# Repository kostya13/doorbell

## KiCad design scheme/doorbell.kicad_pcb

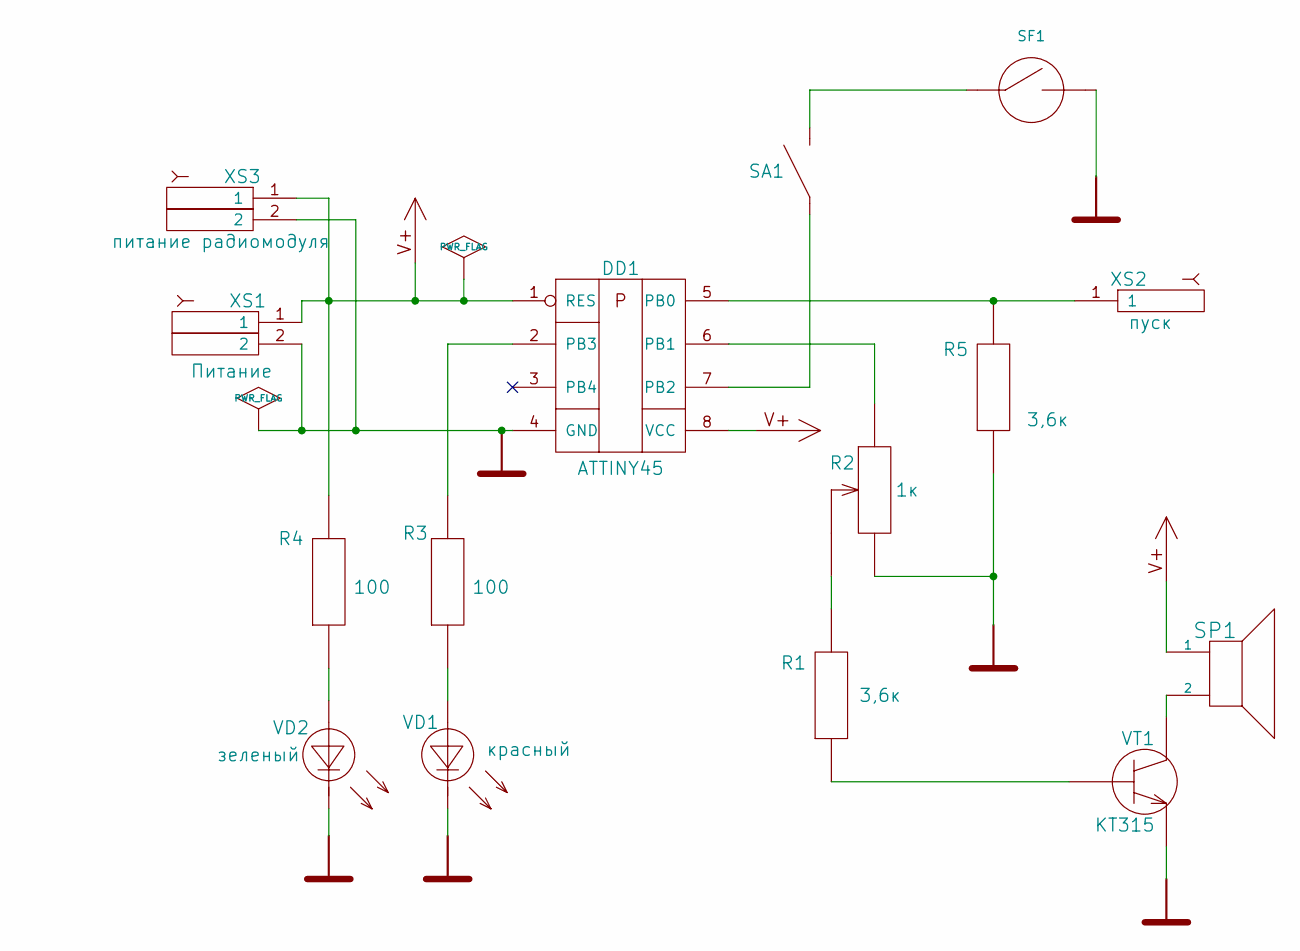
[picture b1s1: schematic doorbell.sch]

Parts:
DD1: ATTINY45
R1: 3,6к
R2: 1к
R3, R4: 100
R5: 3,6к
SA1: SA
SF1: SF
SP1: SPEAKER
VD1: красный
VD2: зеленый
VT1: КТ315
XS1: Питание
XS2: пуск
XS3: питание радиомодуля

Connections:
GND: DD1.4 (GND), R2.3, R5.1, SF1.1, VD1.1, VD2.1, VT1.3 (E), XS1.2, XS3.2
unnamed: R1.1, VT1.1 (B)
unnamed: R3.1, VD1.2
unnamed: R4.1, VD2.2
unnamed: DD1.2 (PB3), R3.2
unnamed: SP1.2, VT1.2 (C)
unnamed: DD1.6 (PB1), R2.1
unnamed: SA1.1, SF1.2
unnamed: R1.2, R2.2
unnamed: DD1.5 (PB0), R5.2, XS2.1
unnamed: DD1.7 (PB2), SA1.2
V+: DD1.1 (RES), DD1.8 (VCC), R4.2, SP1.1, XS1.1, XS3.1

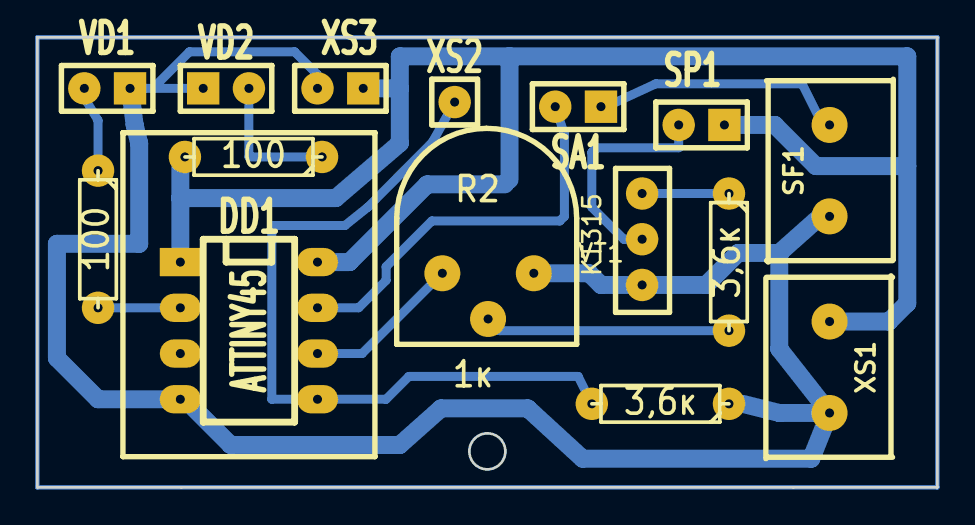
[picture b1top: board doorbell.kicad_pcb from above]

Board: 2 copper layers, 50.0 x 25.0 mm, 15 parts (0 on the bottom side), 12 nets.

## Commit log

2014-02-27 add stop/start buttons
2014-02-27 small fixes
2014-03-02 add kicad schemes
2014-03-03 next step
2014-03-04 small changes
